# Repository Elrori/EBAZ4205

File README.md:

# EBAZ4205

EBIT EBAZ4205 ZYNQ7Z010 BOARD.

EBAZ4205是EBIT BTC矿机的控制板，是最便宜的矿板，其他还有EBAZ4203等。EBAZ4205板载一块Xilinx ZYNQ7Z010 SOC、256MB DDR3内存、一块128MB NAND和100M以太网PHY等。原理图和PCB从二手商获得。默认情况下，板子需要从2.0mm的PHD排针供电，电压5V-12V。Linux默认从NAND启动并执行挖矿控制程序。板子有SD卡接口，可以自己焊接SD卡接口，并更改电阻，使ZYNQ从SD启动。板子价格便宜适合用于学习ZYNQ。但是，比较遗憾的是ZYNQ的USB引脚并未引出。

- 裸机程序固化方法(原始板子)

  文章[链接](https://www.jianshu.com/p/b83c663ecaaa)

- u-boot&Linux生成方法记录(SD卡启动)

  文章[链接](https://www.jianshu.com/p/370f95f0068f)

- EBAZ4205+HDMI视频软解测试(SD卡启动)

  文章[链接](https://www.jianshu.com/p/f035751c2fe5)

- EBAZ420x OpenWrt Release.

  [Elrori/openwrt-auto](https://github.com/Elrori/openwrt-auto)
  
  [将EBAZ4205变为OpenWrt旁路由](https://blog.csdn.net/z951573431/article/details/123819564)

- 其他资料

  [其他关联repo(en)](https://github.com/xjtuecho/EBAZ4205)
  
  [EBIT S9原理图](https://github.com/openzynqhardware/ebaz4205-openwrt/tree/master/hardware/S9)

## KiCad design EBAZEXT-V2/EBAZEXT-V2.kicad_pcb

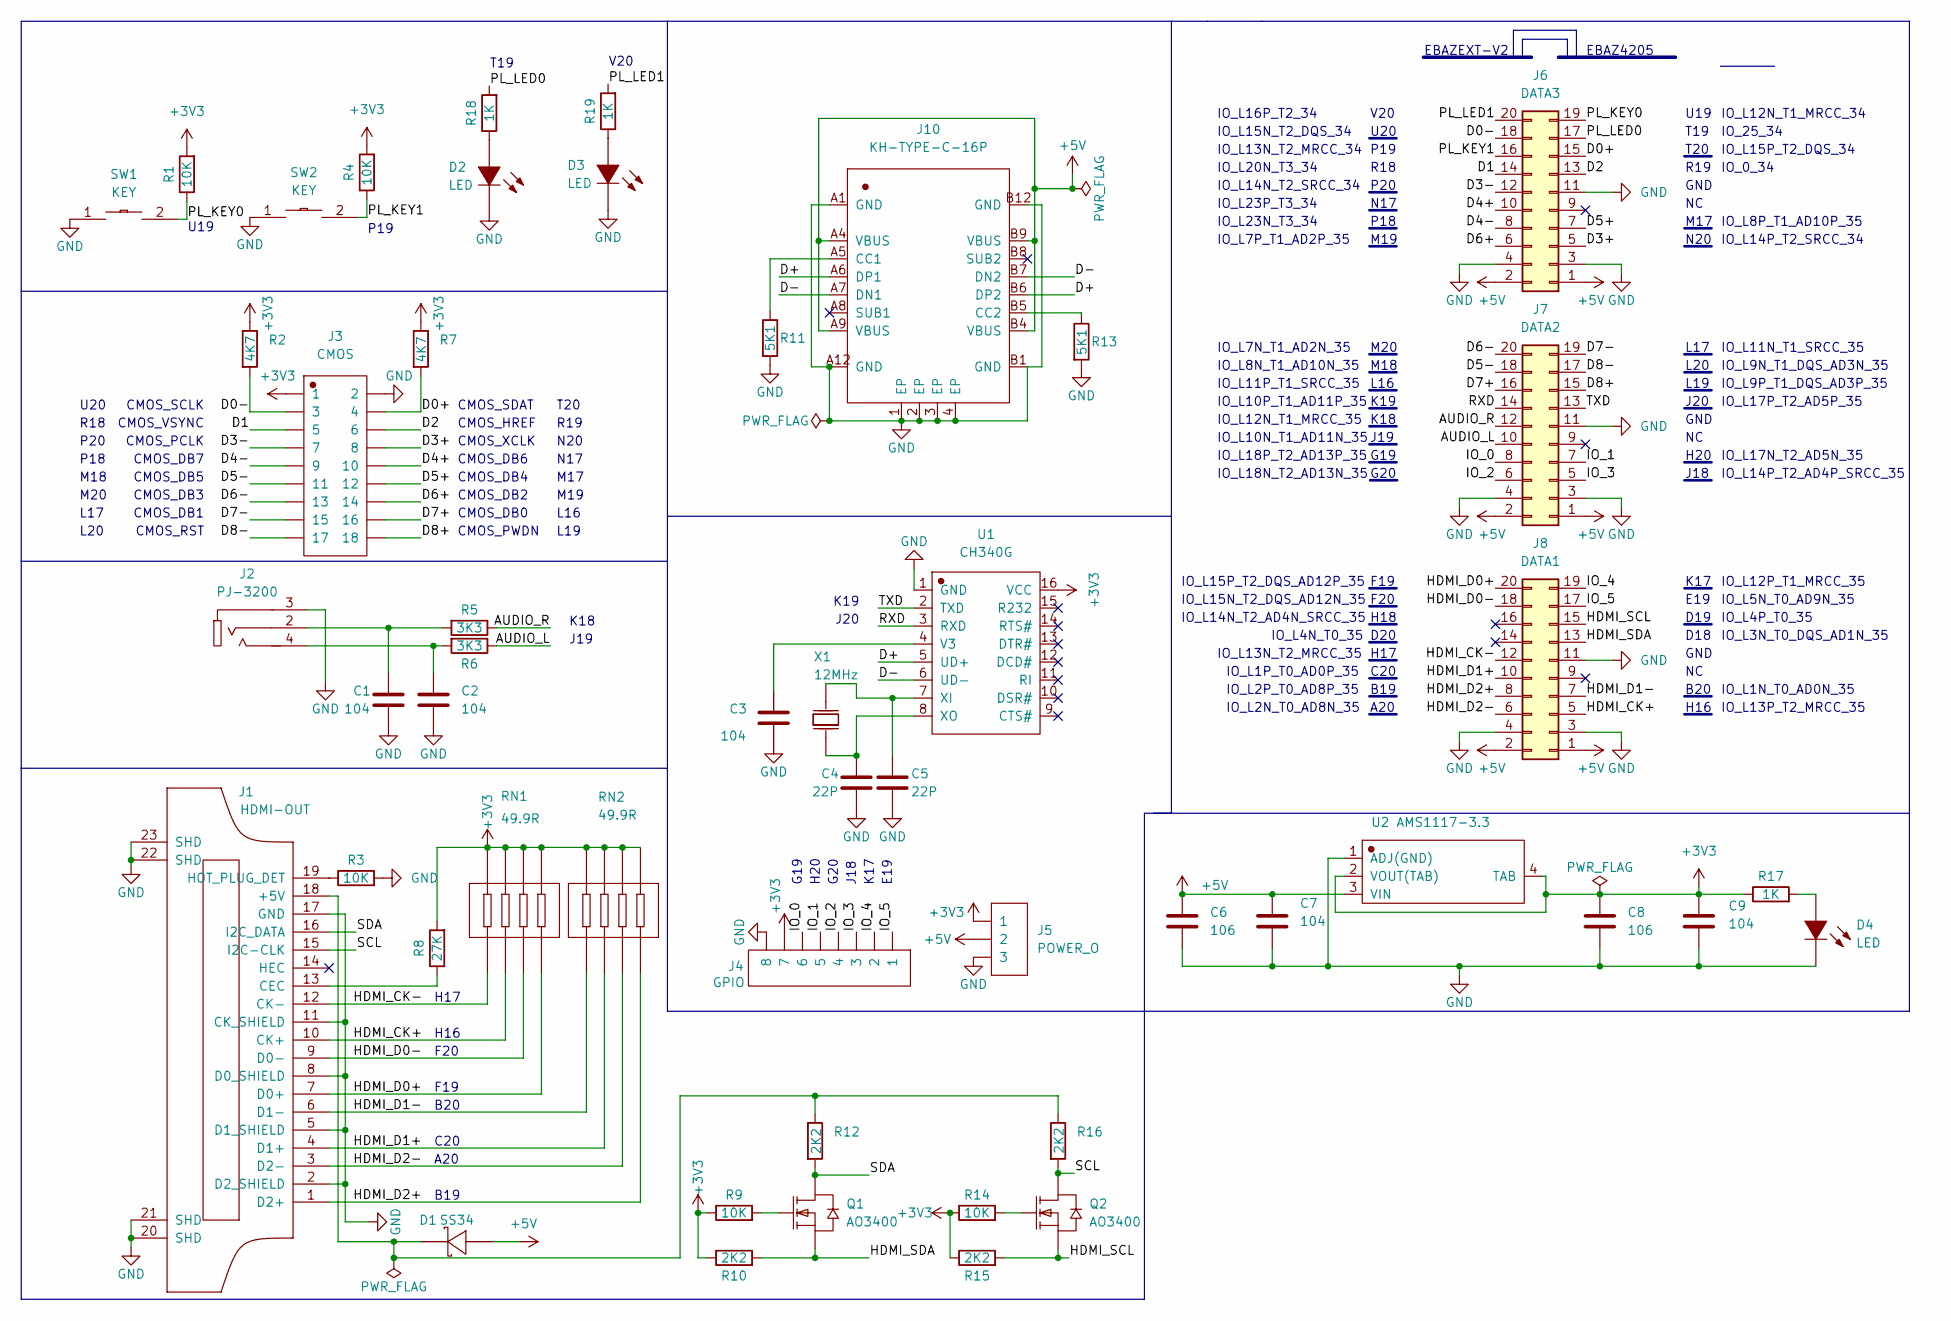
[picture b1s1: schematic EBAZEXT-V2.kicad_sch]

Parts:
C1, C2, C3, C7, C9: 104; C0603
C4, C5: 22P; C0603
C6, C8: 106; C0603
D1: SS34; DO-214AC_L4.3-W2.7-LS5.3-RD
D2, D3, D4: LED; LED0603-FD
J1: HDMI-OUT; HDMI-SMD_HDMI-019S
J2: PJ-3200; AUDIO-TH_PJ-3200
J3: CMOS; HDR-TH_18P-P2.54-V-F-R2-C9-S2.54-1
J4: GPIO; HDR-TH_8P-P2.54-V-F-1
J5: POWER_O; HDR-TH_3P-P2.54-V-M-1
J6: DATA3; EBAZEXT-DAT
J7: DATA2; EBAZEXT-DAT
J8: DATA1; EBAZEXT-DAT
J10: KH-TYPE-C-16P; USB-C-SMD_KH-TYPE-C-16P
Q1, Q2: AO3400; SOT-23_L2.9-W1.3-P1.90-LS2.4-BR
R1, R3, R4, R9, R14: 10K; R0603
R2, R7: 4K7; R0603
R5, R6: 3K3; R0603
R8: 27K; R0603
R10, R12, R15, R16: 2K2; R0603
R11, R13: 5K1; R0603
R17, R18, R19: 1K; R0603
RN1, RN2: 49.9R; RES-ARRAY-SMD_0603-8P-L3.2-W1.6-BL
SW1, SW2: KEY; SW-SMD_L6.0-W3.3-LS8.0
U1: CH340G; SOIC-16_L9.9-W3.9-P1.27-LS6.0-BL
U2: AMS1117-3.3; SOT-223-4_L6.5-W3.5-P2.30-LS7.0-BR
X1: 12MHz; HC-49S_L11.4-W4.8

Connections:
+3V3: C8.1, C9.1, J3.1, J4.7, J5.1, R1.2, R2.1, R4.2, R7.1, R8.2, R9.1, R10.1, R14.1, R15.1, R17.1, RN1.5, RN1.6, RN1.7, RN1.8, RN2.5, RN2.6, RN2.7, RN2.8, U1.16 (VCC), U2.2 (VOUT(TAB)), U2.4 (TAB)
+5V: C6.1, C7.1, D1.2 (A), J5.2, J6.1, J6.2, J7.1, J7.2, J8.1, J8.2, J10.A4 (VBUS), J10.A9 (VBUS), J10.B4 (VBUS), J10.B9 (VBUS), U2.3 (VIN)
/AUDIO_L: J7.10, R6.1
/AUDIO_R: J7.12, R5.1
/D0+: J3.4, J6.15, R7.2
/D0-: J3.3, J6.18, R2.2
/D1: J3.5, J6.14
/D2: J3.6, J6.13
/D3+: J3.8, J6.5
/D3-: J3.7, J6.12
/D4+: J3.10, J6.10
/D4-: J3.9, J6.8
/D5+: J3.12, J6.7
/D5-: J3.11, J7.18
/D6+: J3.14, J6.6
/D6-: J3.13, J7.20
/D7+: J3.16, J7.16
/D7-: J3.15, J7.19
/D8+: J3.18, J7.15
/D8-: J3.17, J7.17
/D+: J10.A6 (DP1), J10.B6 (DP2), U1.5 (UD+)
/D-: J10.A7 (DN1), J10.B7 (DN2), U1.6 (UD-)
/HDMI_CK+: J1.10 (CK+), J8.5, RN1.2
/HDMI_CK-: J1.12 (CK-), J8.12, RN1.1
/HDMI_D0+: J1.7 (D0+), J8.20, RN1.4
/HDMI_D0-: J1.9 (D0-), J8.18, RN1.3
/HDMI_D1+: J1.4 (D1+), J8.10, RN2.2
/HDMI_D1-: J1.6 (D1-), J8.7, RN2.1
/HDMI_D2+: J1.1 (D2+), J8.8, RN2.4
/HDMI_D2-: J1.3 (D2-), J8.6, RN2.3
/HDMI_SCL: J8.15, Q2.2 (S), R15.2
/HDMI_SDA: J8.13, Q1.2 (S), R10.2
/IO_0: J4.6, J7.8
/IO_1: J4.5, J7.7
/IO_2: J4.4, J7.6
/IO_3: J4.3, J7.5
/IO_4: J4.2, J8.19
/IO_5: J4.1, J8.17
/PL_KEY0: J6.19, R1.1, SW1.2
/PL_KEY1: J6.16, R4.1, SW2.2
/PL_LED0: J6.17, R18.2
/PL_LED1: J6.20, R19.2
/RXD: J7.14, U1.3 (RXD)
/SCL: J1.15 (I2C-CLK), Q2.3 (D), R16.2
/SDA: J1.16 (I2C_DATA), Q1.3 (D), R12.2
/TXD: J7.13, U1.2 (TXD)
GND: C1.2, C2.2, C3.2, C4.2, C5.2, C6.2, C7.2, C8.2, C9.2, D2.2 (K), D3.2 (K), D4.2 (K), J1.2 (D2_SHIELD), J1.5 (D1_SHIELD), J1.8 (D0_SHIELD), J1.11 (CK_SHIELD), J1.17 (GND), J1.20 (SHD), J1.21 (SHD), J1.22 (SHD), J1.23 (SHD), J2.3, J3.2, J4.8, J5.3, J6.3, J6.4, J6.11, J7.3, J7.4, J7.11, J8.3, J8.4, J8.11, J10.1 (EP), J10.2 (EP), J10.3 (EP), J10.4 (EP), J10.A1 (GND), J10.A12 (GND), J10.B1 (GND), J10.B12 (GND), R3.2, R11.2, R13.2, SW1.1, SW2.1, U1.1 (GND), U2.1 (ADJ(GND))
unnamed: C1.1, J2.2, R5.2
unnamed: C2.1, J2.4, R6.2
unnamed: C3.1, U1.4 (V3)
unnamed: C4.1, U1.8 (XO), X1.2 (OSC2)
unnamed: C5.1, U1.7 (XI), X1.1 (OSC1)
unnamed: D1.1 (K), J1.18 (+5V), R12.1, R16.1
unnamed: D2.1 (A), R18.1
unnamed: D3.1 (A), R19.1
unnamed: D4.1 (A), R17.2
unnamed: J1.13 (CEC), R8.1
unnamed: J1.19 (HOT_PLUG_DET), R3.1
unnamed: J10.A5 (CC1), R11.1
unnamed: J10.B5 (CC2), R13.1
unnamed: Q1.1 (G), R9.2
unnamed: Q2.1 (G), R14.2

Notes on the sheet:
IO_L17P_T2_AD5P_35
CMOS_DB4
IO_L2N_T0_AD8N_35
M18
M17
IO_L1P_T0_AD0P_35
M20
CMOS_SCLK
IO_L14P_T2_SRCC_34
IO_L11P_T1_SRCC_35
CMOS_XCLK
IO_0_34
IO_L1N_T0_AD0N_35
A20
F20
CMOS_DB1
K17
B20
IO_L9P_T1_DQS_AD3P_35
IO_L7N_T1_AD2N_35
L16
IO_L3N_T0_DQS_AD1N_35
R18
IO_L12N_T1_MRCC_34
IO_25_34
V20
H20
J19
IO_L18N_T2_AD13N_35
GND
N20
CMOS_DB2
L19
CMOS_PCLK
IO_L23P_T3_34
IO_L13N_T2_MRCC_35
T19
IO_L11N_T1_SRCC_35
IO_L5N_T0_AD9N_35
L17

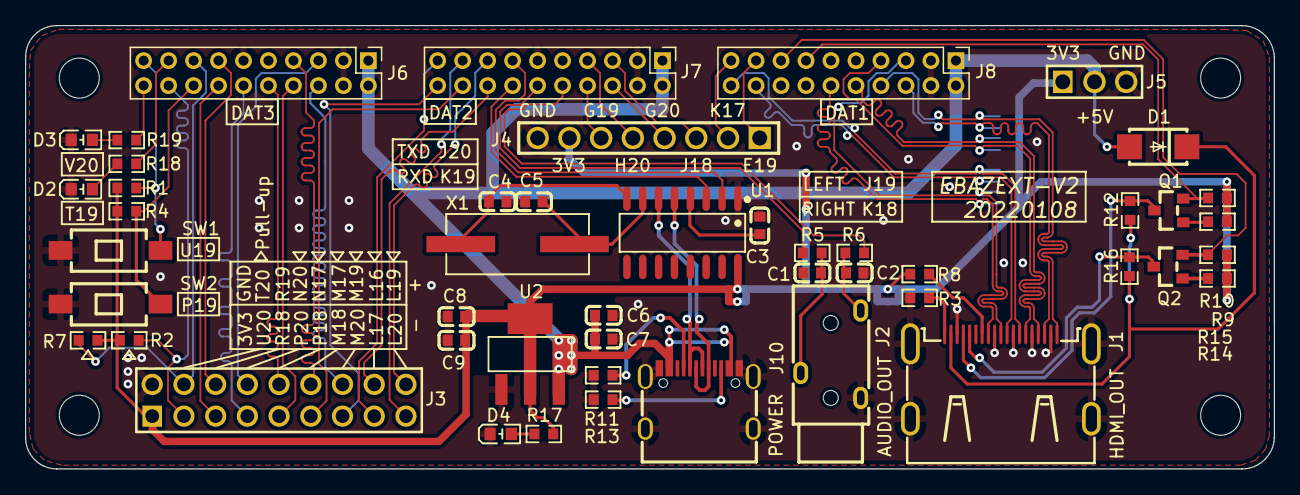
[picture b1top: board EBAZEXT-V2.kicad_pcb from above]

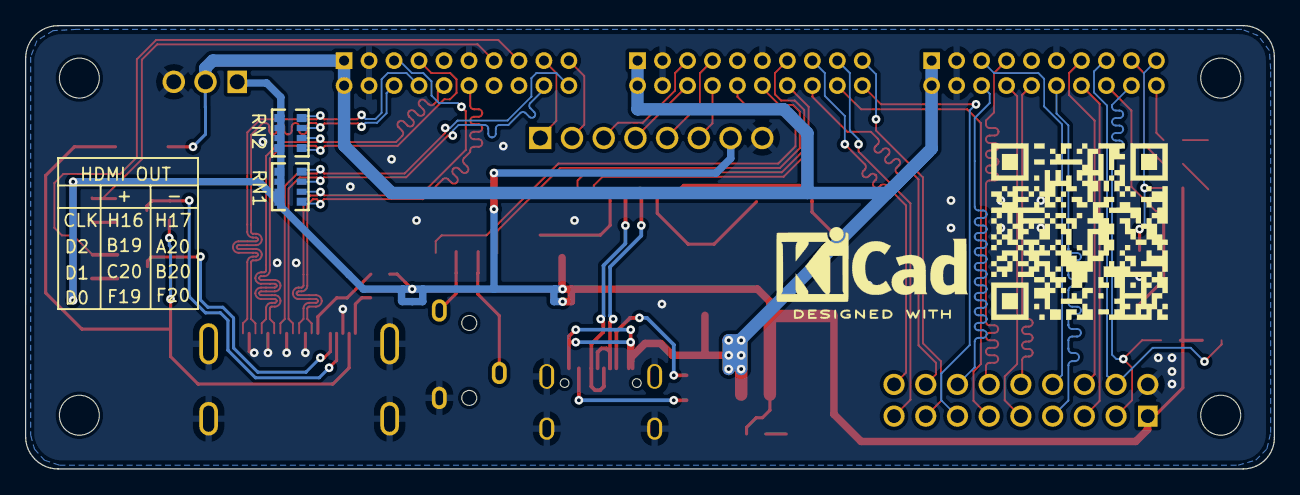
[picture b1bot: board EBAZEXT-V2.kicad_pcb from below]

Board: 2 copper layers, 100.0 x 35.5 mm, 52 parts (4 on the bottom side), 62 nets.

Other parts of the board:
G1: QRCode; LOGO
G2: KiCad-Logo2_6mm_SilkScreen

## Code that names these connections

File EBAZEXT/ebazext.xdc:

########################################################################
### EBAZEXT pin
########################################################################
set_property PACKAGE_PIN T19 [get_ports {pl_led0}]
set_property IOSTANDARD LVCMOS33 [get_ports {pl_led0}]
set_property PACKAGE_PIN V20 [get_ports {pl_led1}]
set_property IOSTANDARD LVCMOS33 [get_ports {pl_led1}]
set_property PACKAGE_PIN U19 [get_ports {pl_key0}]
set_property IOSTANDARD LVCMOS33 [get_ports {pl_key0}]
set_property PACKAGE_PIN U20 [get_ports {pl_key1}]
set_property IOSTANDARD LVCMOS33 [get_ports {pl_key1}]

set_property PACKAGE_PIN P19 [get_ports {cmos_pclk}]
set_property IOSTANDARD LVCMOS33 [get_ports {cmos_pclk}]
set_property PACKAGE_PIN T20 [get_ports {cmos_sdat}]
set_property IOSTANDARD LVCMOS33 [get_ports {cmos_sdat}]
set_property PACKAGE_PIN R18 [get_ports {cmos_sclk}]
set_property IOSTANDARD LVCMOS33 [get_ports {cmos_sclk}]
set_property PACKAGE_PIN R19 [get_ports {cmos_href}]
set_property IOSTANDARD LVCMOS33 [get_ports {cmos_href}]
set_property PACKAGE_PIN P20 [get_ports {cmos_xclk}]
set_property IOSTANDARD LVCMOS33 [get_ports {cmos_xclk}]
set_property PACKAGE_PIN N17 [get_ports {cmos_vsync}]
set_property IOSTANDARD LVCMOS33 [get_ports {cmos_vsync}]
set_property PACKAGE_PIN L16 [get_ports {cmos_pwdn}]
set_property IOSTANDARD LVCMOS33 [get_ports {cmos_pwdn}]
set_property PACKAGE_PIN L19 [get_ports {cmos_rst}]
set_property IOSTANDARD LVCMOS33 [get_ports {cmos_rst}]
set_property PACKAGE_PIN M17 [get_ports {cmos_db[7]}]
set_property IOSTANDARD LVCMOS33 [get_ports {cmos_db[7]}]
set_property PACKAGE_PIN P18 [get_ports {cmos_db[6]}]
set_property IOSTANDARD LVCMOS33 [get_ports {cmos_db[6]}]
set_property PACKAGE_PIN N20 [get_ports {cmos_db[5]}]
set_property IOSTANDARD LVCMOS33 [get_ports {cmos_db[5]}]
set_property PACKAGE_PIN M19 [get_ports {cmos_db[4]}]
set_property IOSTANDARD LVCMOS33 [get_ports {cmos_db[4]}]
set_property PACKAGE_PIN M20 [get_ports {cmos_db[3]}]
set_property IOSTANDARD LVCMOS33 [get_ports {cmos_db[3]}]
set_property PACKAGE_PIN L17 [get_ports {cmos_db[2]}]
set_property IOSTANDARD LVCMOS33 [get_ports {cmos_db[2]}]
set_property PACKAGE_PIN M18 [get_ports {cmos_db[1]}]
set_property IOSTANDARD LVCMOS33 [get_ports {cmos_db[1]}]
set_property PACKAGE_PIN L20 [get_ports {cmos_db[0]}]
set_property IOSTANDARD LVCMOS33 [get_ports {cmos_db[0]}]

set_property PACKAGE_PIN K19 [get_ports {rxd}]
set_property IOSTANDARD LVCMOS33 [get_ports {rxd}]
set_property PACKAGE_PIN J20 [get_ports {txd}]
set_property IOSTANDARD LVCMOS33 [get_ports {txd}]

set_property PACKAGE_PIN K18 [get_ports {audio_r}]
set_property IOSTANDARD LVCMOS33 [get_ports {audio_r}]
set_property PACKAGE_PIN J19 [get_ports {audio_l}]
set_property IOSTANDARD LVCMOS33 [get_ports {audio_l}]

set_property PACKAGE_PIN G19 [get_ports {vga_hs}]
set_property IOSTANDARD LVCMOS33 [get_ports {vga_hs}]
set_property PACKAGE_PIN H20 [get_ports {vga_vs}]
set_property IOSTANDARD LVCMOS33 [get_ports {vga_vs}]
set_property PACKAGE_PIN G20 [get_ports {vgad[0]}]
set_property IOSTANDARD LVCMOS33 [get_ports {vgad[0]}]
set_property PACKAGE_PIN J18 [get_ports {vgad[1]}]
set_property IOSTANDARD LVCMOS33 [get_ports {vgad[1]}]
set_property PACKAGE_PIN F19 [get_ports {vgad[2]}]
set_property IOSTANDARD LVCMOS33 [get_ports {vgad[2]}]
set_property PACKAGE_PIN K17 [get_ports {vgad[3]}]
set_property IOSTANDARD LVCMOS33 [get_ports {vgad[3]}]
set_property PACKAGE_PIN F20 [get_ports {vgad[4]}]
set_property IOSTANDARD LVCMOS33 [get_ports {vgad[4]}]
set_property PACKAGE_PIN E19 [get_ports {vgad[5]}]
set_property IOSTANDARD LVCMOS33 [get_ports {vgad[5]}]
set_property PACKAGE_PIN H18 [get_ports {vgad[6]}]
set_property IOSTANDARD LVCMOS33 [get_ports {vgad[6]}]
set_property PACKAGE_PIN D19 [get_ports {vgad[7]}]
set_property IOSTANDARD LVCMOS33 [get_ports {vgad[7]}]
set_property PACKAGE_PIN D20 [get_ports {vgad[8]}]
set_property IOSTANDARD LVCMOS33 [get_ports {vgad[8]}]
set_property PACKAGE_PIN D18 [get_ports {vgad[9]}]
set_property IOSTANDARD LVCMOS33 [get_ports {vgad[9]}]
set_property PACKAGE_PIN H17 [get_ports {vgad[10]}]
set_property IOSTANDARD LVCMOS33 [get_ports {vgad[10]}]
set_property PACKAGE_PIN C20 [get_ports {vgad[11]}]
set_property IOSTANDARD LVCMOS33 [get_ports {vgad[11]}]
set_property PACKAGE_PIN B19 [get_ports {vgad[12]}]
set_property IOSTANDARD LVCMOS33 [get_ports {vgad[12]}]
set_property PACKAGE_PIN B20 [get_ports {vgad[13]}]
set_property IOSTANDARD LVCMOS33 [get_ports {vgad[13]}]
set_property PACKAGE_PIN A20 [get_ports {vgad[14]}]
set_property IOSTANDARD LVCMOS33 [get_ports {vgad[14]}]
set_property PACKAGE_PIN H16 [get_ports {vgad[15]}]
set_property IOSTANDARD LVCMOS33 [get_ports {vgad[15]}]

########################################################################
### EBAZ4205  pin
########################################################################
set_property PACKAGE_PIN W13 [get_ports {led_r}]
set_property PACKAGE_PIN W14 [get_ports {led_g}]
set_property IOSTANDARD LVCMOS33 [get_ports {led_r}]
set_property IOSTANDARD LVCMOS33 [get_ports {led_g}]
set_property PACKAGE_PIN W15 [get_ports {mdio_rtl_0_mdc}]
set_property PACKAGE_PIN Y14 [get_ports {mdio_rtl_0_mdio_io}]
set_property PACKAGE_PIN U14 [get_ports {mii_rtl_0_rx_clk}]
set_property PACKAGE_PIN W16 [get_ports {mii_rtl_0_rx_dv}]
set_property PACKAGE_PIN Y16 [get_ports {mii_rtl_0_rxd[0]}]
set_property PACKAGE_PIN V16 [get_ports {mii_rtl_0_rxd[1]}]
set_property PACKAGE_PIN V17 [get_ports {mii_rtl_0_rxd[2]}]
set_property PACKAGE_PIN Y17 [get_ports {mii_rtl_0_rxd[3]}]
set_property PACKAGE_PIN U15 [get_ports {mii_rtl_0_tx_clk}]
set_property PACKAGE_PIN W19 [get_ports {mii_rtl_0_tx_en}]
set_property PACKAGE_PIN W18 [get_ports {mii_rtl_0_txd[0]}]
set_property PACKAGE_PIN Y18 [get_ports {mii_rtl_0_txd[1]}]
set_property PACKAGE_PIN V18 [get_ports {mii_rtl_0_txd[2]}]
set_property PACKAGE_PIN Y19 [get_ports {mii_rtl_0_txd[3]}]
set_property IOSTANDARD LVCMOS33 [get_ports {mdio_rtl_0_mdc}]
set_property IOSTANDARD LVCMOS33 [get_ports {mdio_rtl_0_mdio_io}]
set_property IOSTANDARD LVCMOS33 [get_ports {mii_rtl_0_rx_clk}]
set_property IOSTANDARD LVCMOS33 [get_ports {mii_rtl_0_rx_dv}]
set_property IOSTANDARD LVCMOS33 [get_ports {mii_rtl_0_rxd[0]}]
set_property IOSTANDARD LVCMOS33 [get_ports {mii_rtl_0_rxd[1]}]
set_property IOSTANDARD LVCMOS33 [get_ports {mii_rtl_0_rxd[2]}]
set_property IOSTANDARD LVCMOS33 [get_ports {mii_rtl_0_rxd[3]}]
set_property IOSTANDARD LVCMOS33 [get_ports {mii_rtl_0_tx_clk}]
set_property IOSTANDARD LVCMOS33 [get_ports {mii_rtl_0_tx_en}]
set_property IOSTANDARD LVCMOS33 [get_ports {mii_rtl_0_txd[0]}]
set_property IOSTANDARD LVCMOS33 [get_ports {mii_rtl_0_txd[1]}]
set_property IOSTANDARD LVCMOS33 [get_ports {mii_rtl_0_txd[2]}]
set_property IOSTANDARD LVCMOS33 [get_ports {mii_rtl_0_txd[3]}]
########################################################################
### other constraint
########################################################################

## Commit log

2021-12-17 vga external board
2022-01-13 vga ext
2022-01-13 vga expansion
2022-02-10 uboot
2022-03-27 add dts
2022-03-28 add ps7_init_gpl.c,modify hdf
2022-03-29 add EBAZEXT-V2
2022-03-29 add png
2022-03-29 modify README.md
2022-05-21 modify
